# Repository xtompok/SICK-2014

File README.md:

SICK 2014
=========

Repozitar pro soutez SICK Robot Day 2014

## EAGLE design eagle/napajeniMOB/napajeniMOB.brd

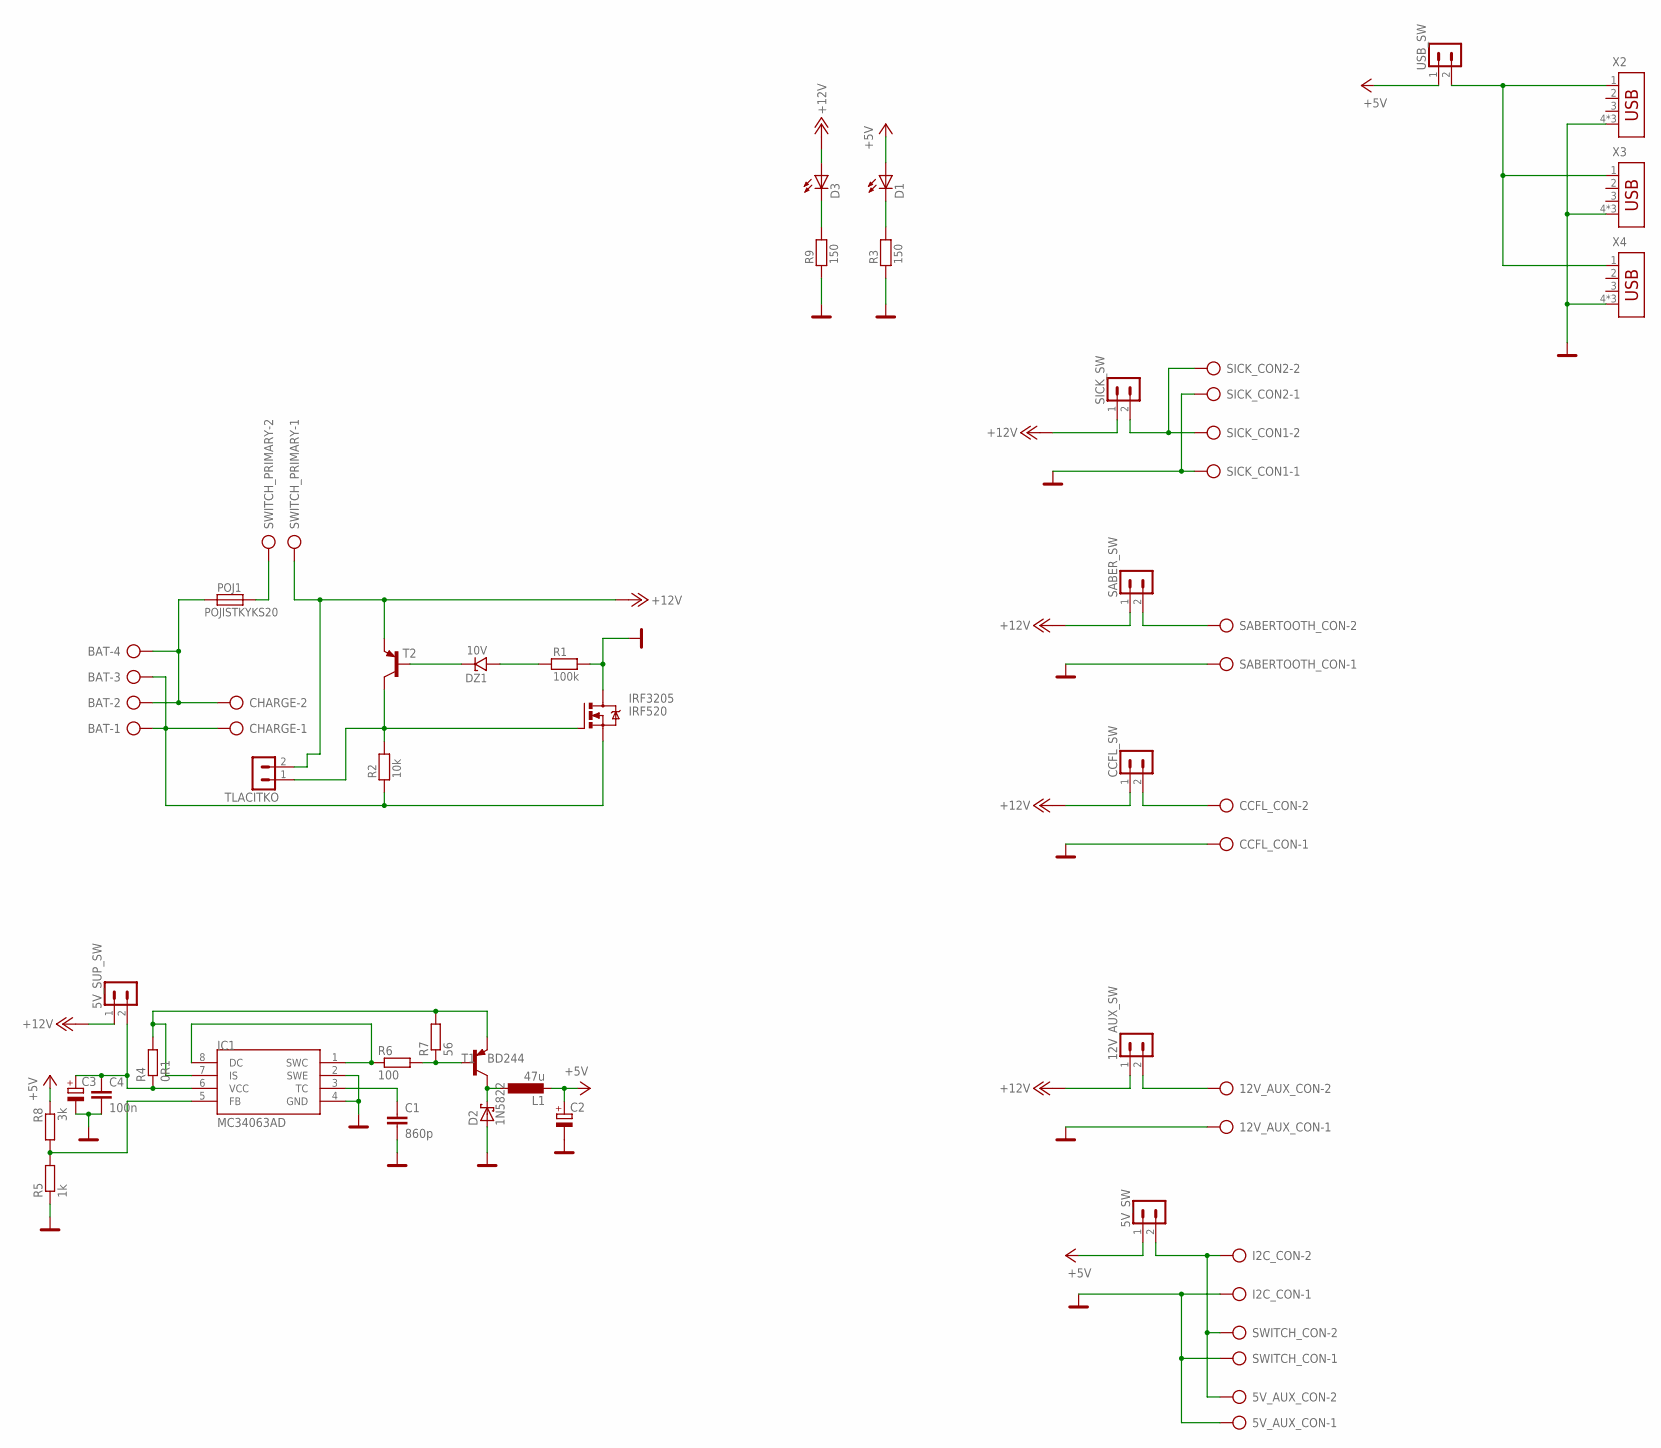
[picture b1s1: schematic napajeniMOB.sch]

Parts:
5V_AUX_CON, 12V_AUX_CON: AK500/2
5V_SUP_SW, 5V_SW, 12V_AUX_SW: PSH02-02P
BAT: AK500/4
C1: 860p; C0805
C2, C3: CPOL-EUE5-8.5; E5-8,5
C4: 100n; C0805
CCFL_CON: AK500/2
CCFL_SW: PSH02-02P
CHARGE: AK500/2
D1, D3: LED3MM
D2: 1N5822; DO41-7.6
DZ1: 10V; SOD-80
I2C_CON: AK500/2
IC1: MC34063AD; SOIC8
IRF3205: IRF520; TO220BV
L1: 47u; TJ3-U1
POJ1: POJISTKYKS20; POJ_KS20
R1: 100k; 0805
R2: 10k; 0805
R3, R9: 150; 0805
R4: 0R1; M0805
R5: 1k; M0805
R6: 100; M0805
R7: 56; M0805
R8: 3k; M0805
SABERTOOTH_CON: AK500/2
SABER_SW: PSH02-02P
SICK_CON1, SICK_CON2: AK500/2
SICK_SW: PSH02-02P
SWITCH_CON: AK500/2
SWITCH_PRIMARY: AK500/2
T1: BD244; TO220
T2: BC807-16-PNP-SOT23-BEC; SOT23-BEC
TLACITKO: PSH02-02P
USB_SW: PSH02-02P
X2, X3, X4: USB-787616GROUNDED; USBGROUNDED

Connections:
+5V: 5V_SW.1, C2.+, D1.A, L1.2, R8.1, USB_SW.1
+12V: 5V_SUP_SW.1, 12V_AUX_SW.1, CCFL_SW.1, D3.A, SABER_SW.1, SICK_SW.1, SWITCH_PRIMARY.1, T2.E, TLACITKO.2
GND: 5V_AUX_CON.1, 12V_AUX_CON.1, C1.2, C2.-, C3.-, C4.2, CCFL_CON.1, D2.A, I2C_CON.1, IC1.2 (SWE), IC1.4 (GND), IRF3205.D, R1.2, R3.1, R5.1, R9.1, SABERTOOTH_CON.1, SICK_CON1.1, SICK_CON2.1, SWITCH_CON.1, X2.4, X2.S1 (4), X2.S2 (4), X3.4, X3.S1 (4), X3.S2 (4), X4.4, X4.S1 (4), X4.S2 (4)
GND_BATERIE: BAT.1, BAT.3, CHARGE.1, IRF3205.S, R2.1
unnamed: DZ1.A, R1.1
unnamed: BAT.2, BAT.4, CHARGE.2, POJ1.1
unnamed: DZ1.K, T2.B
unnamed: POJ1.2, SWITCH_PRIMARY.2
unnamed: IRF3205.G, R2.2, T2.C, TLACITKO.1
unnamed: 5V_SUP_SW.2, C3.+, C4.1, IC1.6 (VCC), R4.1
unnamed: D3.K (C), R9.2
unnamed: D1.K (C), R3.2
unnamed: SICK_CON1.2, SICK_CON2.2, SICK_SW.2
unnamed: USB_SW.2, X2.1, X3.1, X4.1
unnamed: SABERTOOTH_CON.2, SABER_SW.2
unnamed: CCFL_CON.2, CCFL_SW.2
unnamed: D2.C, L1.1, T1.2 (C)
unnamed: 12V_AUX_CON.2, 12V_AUX_SW.2
unnamed: 5V_AUX_CON.2, 5V_SW.2, I2C_CON.2, SWITCH_CON.2
unnamed: IC1.5 (FB), R5.2, R8.2
unnamed: IC1.7 (IS), R4.2, R7.2, T1.3 (E)
unnamed: IC1.1 (SWC), IC1.8 (DC), R6.1
unnamed: R6.2, R7.1, T1.1 (B)
unnamed: C1.1, IC1.3 (TC)

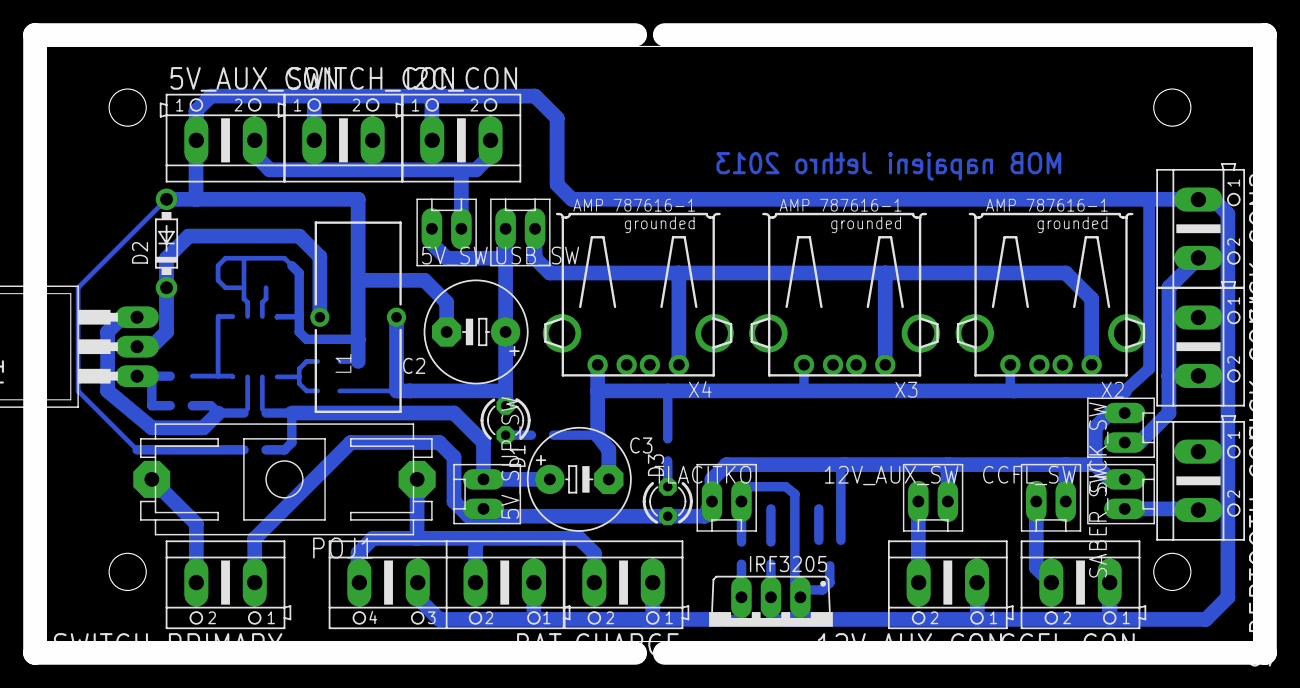
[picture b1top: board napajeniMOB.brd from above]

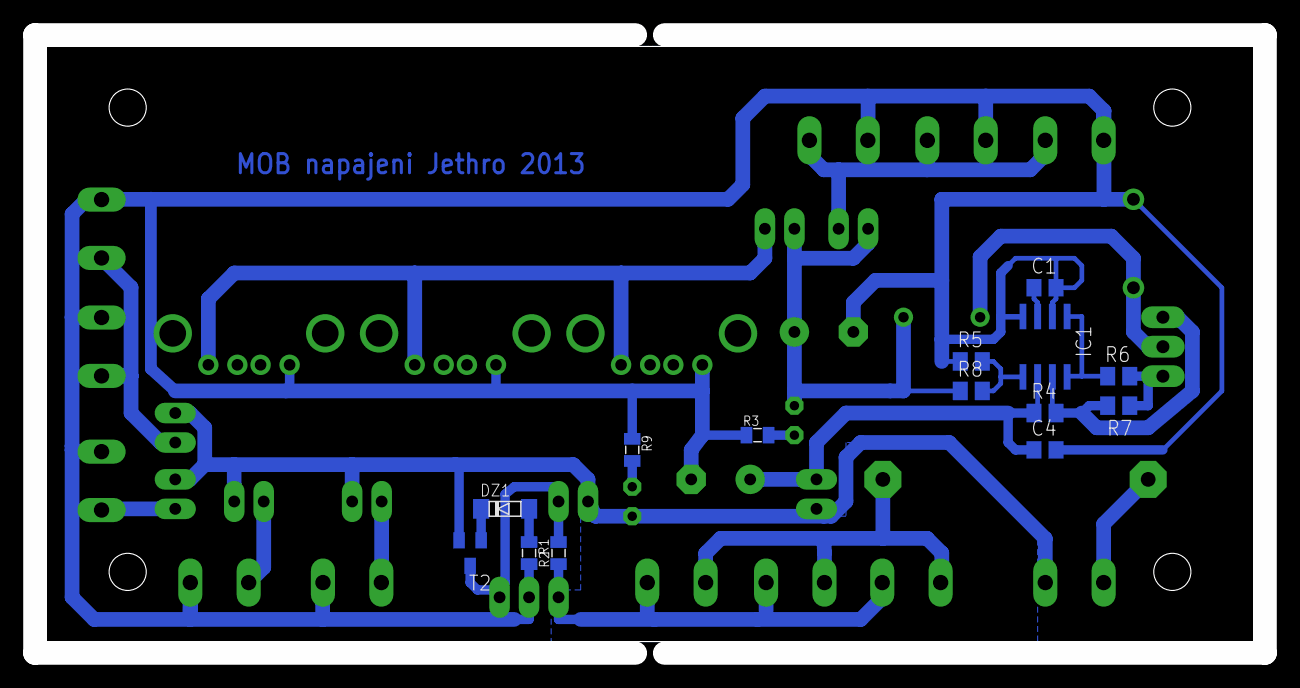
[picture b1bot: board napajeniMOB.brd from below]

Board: 2 copper layers, 106.0 x 53.3 mm, 45 parts (14 on the bottom side), 24 nets.

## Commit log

2013-12-21 Pridana schemata napajeci desky
2013-12-21 Pridan .gitignore, zatim pro soubory eaglu
2013-12-21 Soutez je pristi rok ;-)

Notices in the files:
parts and their libraries:
Copyright (C) PaJa 2001-2011
Copyright (C) Vlada 2004-2005
Copyright (C) PaJa 2011
